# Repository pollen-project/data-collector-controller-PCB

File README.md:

# data-collector-controller-PCB

Design files for the data collector made with KiCAD version 8.0.

## PDF files
* [Schematic](Pollen%20PCB/prints/pollen_sch.pdf)
* [Board](Pollen%20PCB/prints/pollen_pcb.pdf)

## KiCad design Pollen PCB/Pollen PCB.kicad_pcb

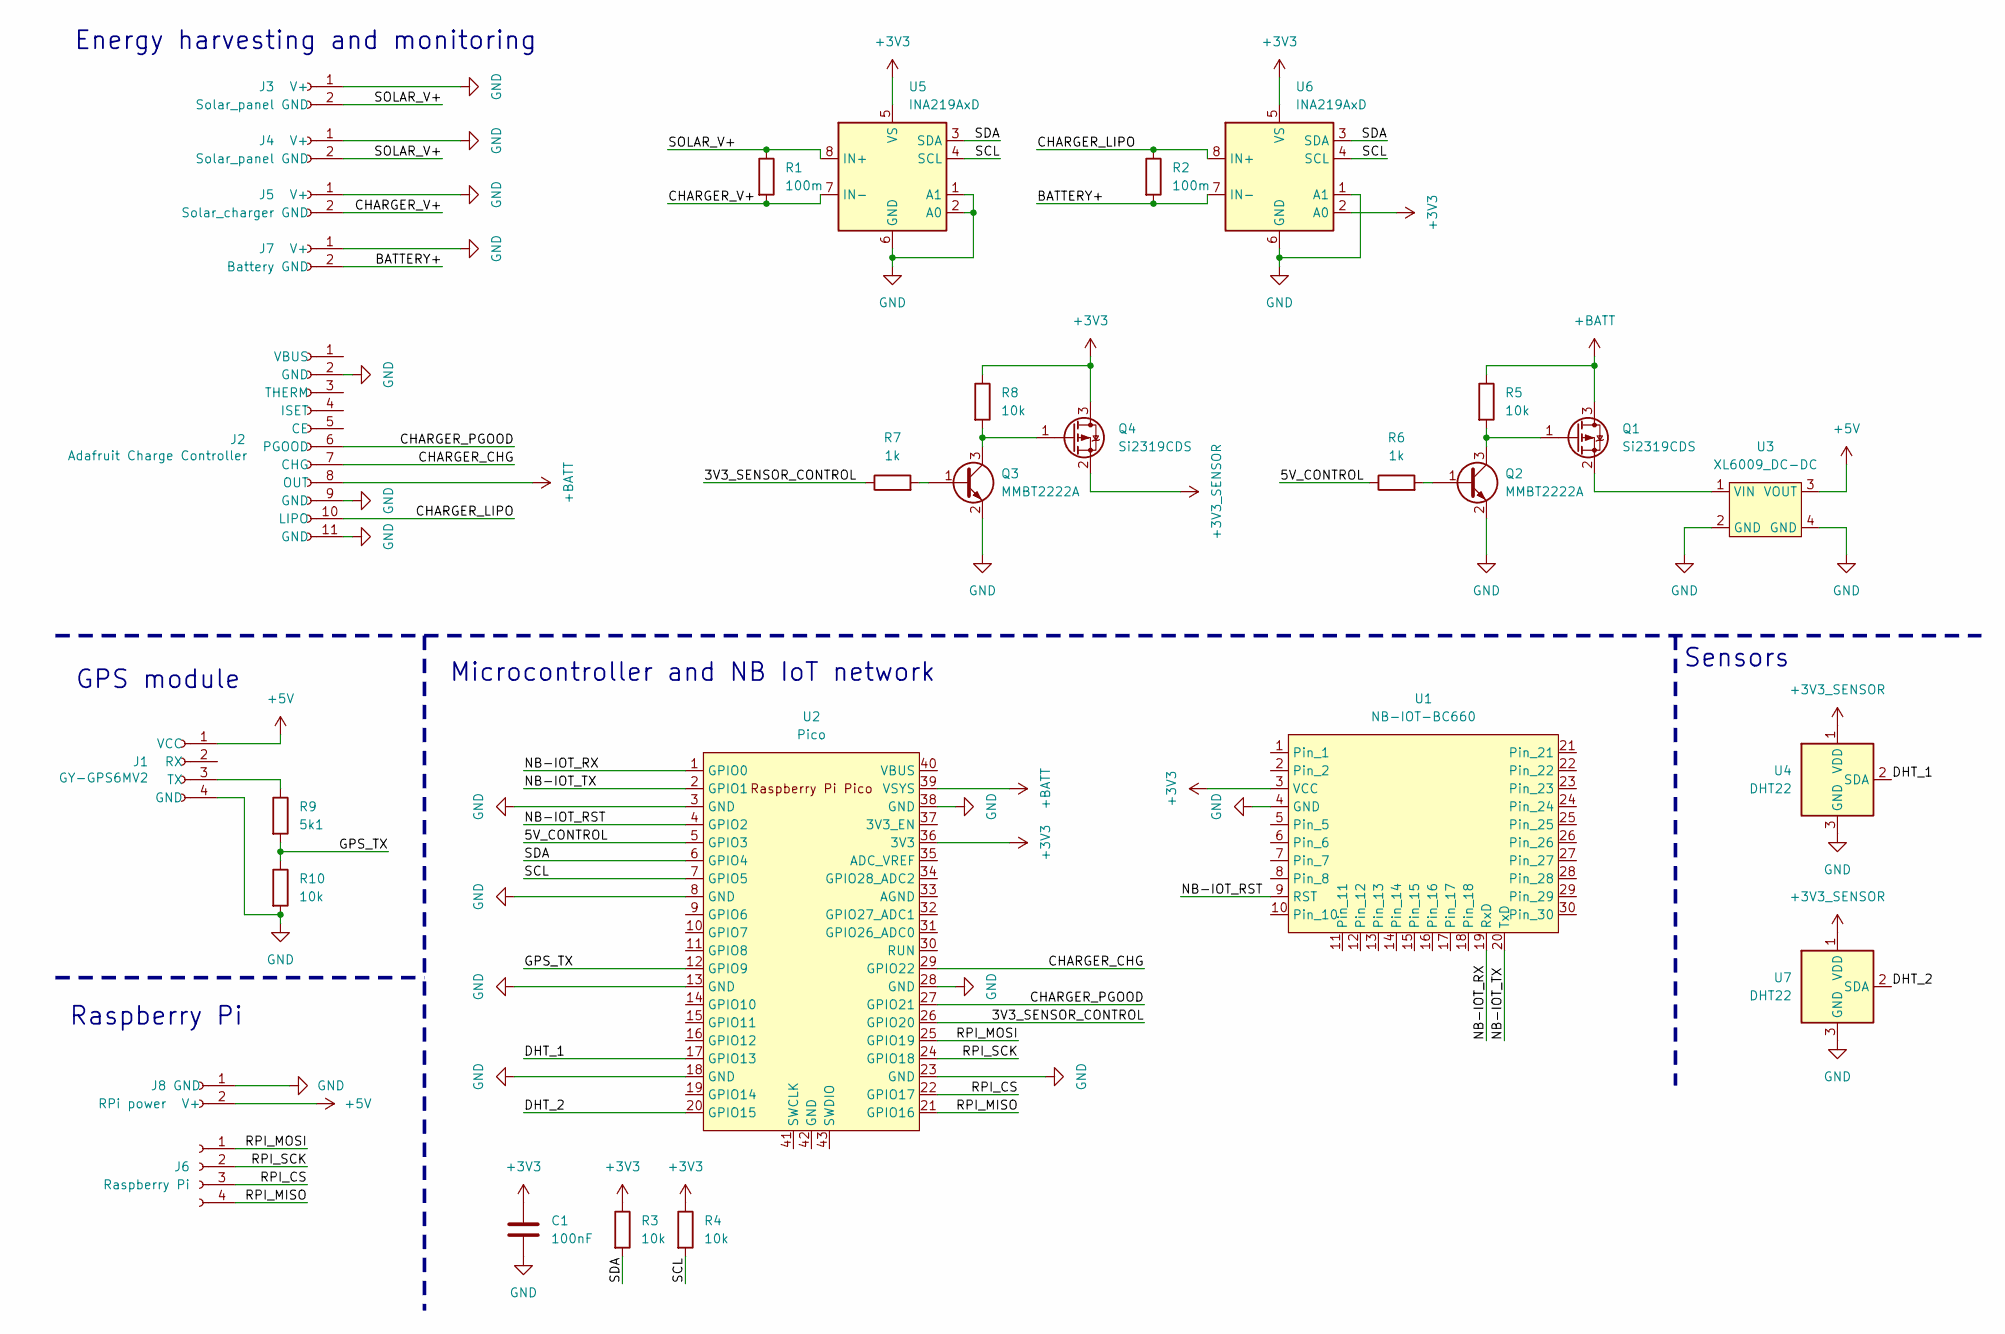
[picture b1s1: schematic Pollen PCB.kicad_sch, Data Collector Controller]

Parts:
C1: 100nF; C_1206_3216Metric_Pad1.33x1.80mm_HandSolder
J1: GY-GPS6MV2; PinSocket_1x04_P2.54mm_Vertical
J2: Adafruit Charge Controller; PinSocket_1x11_P2.54mm_Vertical
J3, J4: Solar_panel; PinSocket_1x02_P2.54mm_Vertical
J5: Solar_charger; PinSocket_1x02_P2.54mm_Vertical
J6: Raspberry Pi; PinSocket_1x04_P2.54mm_Vertical
J7: Battery; PinSocket_1x02_P2.54mm_Vertical
J8: RPi power; PinSocket_1x02_P2.54mm_Vertical
Q1, Q4: Si2319CDS; SOT-23
Q2, Q3: MMBT2222A; SOT-23
R1, R2: 100m; R_2512_6332Metric_Pad1.40x3.35mm_HandSolder
R3, R4, R5, R8, R10: 10k; R_1206_3216Metric_Pad1.30x1.75mm_HandSolder
R6, R7: 1k; R_1206_3216Metric_Pad1.30x1.75mm_HandSolder
R9: 5k1; R_1206_3216Metric_Pad1.30x1.75mm_HandSolder
U1: NB-IOT-BC660
U2: Pico; RPi_Pico_SMD_TH
U3: XL6009_DC-DC
U4, U7: DHT22; ASAIR_AM2302_P2.54mm_Vertical
U5, U6: INA219AxD; SOIC-8_3.9x4.9mm_P1.27mm

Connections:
+3V3: C1.1, Q4.3 (D), R3.1, R4.1, R8.1, U1.3 (VCC), U2.36 (3V3), U5.5 (VS), U6.2 (A0), U6.5 (VS)
+3V3_SENSOR: Q4.2 (S), U4.1 (VDD), U7.1 (VDD)
+5V: J1.1 (VCC), J8.2 (V+), U3.3 (VOUT)
+BATT: J2.8 (OUT), Q1.3 (D), R5.1, U2.39 (VSYS)
/3V3_SENSOR_CONTROL: R7.1, U2.26 (GPIO20)
/5V_CONTROL: R6.1, U2.5 (GPIO3)
/BATTERY+: J7.2 (GND), R2.2, U6.7 (IN-)
/CHARGER_CHG: J2.7 (CHG), U2.29 (GPIO22)
/CHARGER_LIPO: J2.10 (LIPO), R2.1, U6.8 (IN+)
/CHARGER_PGOOD: J2.6 (PGOOD), U2.27 (GPIO21)
/CHARGER_V+: J5.2 (GND), R1.2, U5.7 (IN-)
/DHT_1: U2.17 (GPIO13), U4.2 (SDA)
/DHT_2: U2.20 (GPIO15), U7.2 (SDA)
/GPS_TX: R9.2, R10.1, U2.12 (GPIO9)
/NB-IOT_RST: U1.9 (RST), U2.4 (GPIO2)
/NB-IOT_RX: U1.19 (RxD), U2.1 (GPIO0)
/NB-IOT_TX: U1.20 (TxD), U2.2 (GPIO1)
/RPI_CS: J6.3, U2.22 (GPIO17)
/RPI_MISO: J6.4, U2.21 (GPIO16)
/RPI_MOSI: J6.1, U2.25 (GPIO19)
/RPI_SCK: J6.2, U2.24 (GPIO18)
/SCL: R4.2, U2.7 (GPIO5), U5.4 (SCL), U6.4 (SCL)
/SDA: R3.2, U2.6 (GPIO4), U5.3 (SDA), U6.3 (SDA)
/SOLAR_V+: J3.2 (GND), J4.2 (GND), R1.1, U5.8 (IN+)
GND: C1.2, J1.4 (GND), J2.2 (GND), J2.9 (GND), J2.11 (GND), J3.1 (V+), J4.1 (V+), J5.1 (V+), J7.1 (V+), J8.1 (GND), Q2.2 (E), Q3.2 (E), R10.2, U1.4 (GND), U2.3 (GND), U2.8 (GND), U2.13 (GND), U2.18 (GND), U2.23 (GND), U2.28 (GND), U2.38 (GND), U3.2 (GND), U3.4 (GND), U4.3 (GND), U4.4 (GND), U5.1 (A1), U5.2 (A0), U5.6 (GND), U6.1 (A1), U6.6 (GND), U7.3 (GND), U7.4 (GND)
unnamed: J1.3 (TX), R9.1
unnamed: Q1.1 (G), Q2.3 (C), R5.2
unnamed: Q1.2 (S), U3.1 (VIN)
unnamed: Q2.1 (B), R6.2
unnamed: Q3.1 (B), R7.2
unnamed: Q3.3 (C), Q4.1 (G), R8.2

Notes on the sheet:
Raspberry Pi
Microcontroller and NB IoT network
Sensors
GPS module
Energy harvesting and monitoring

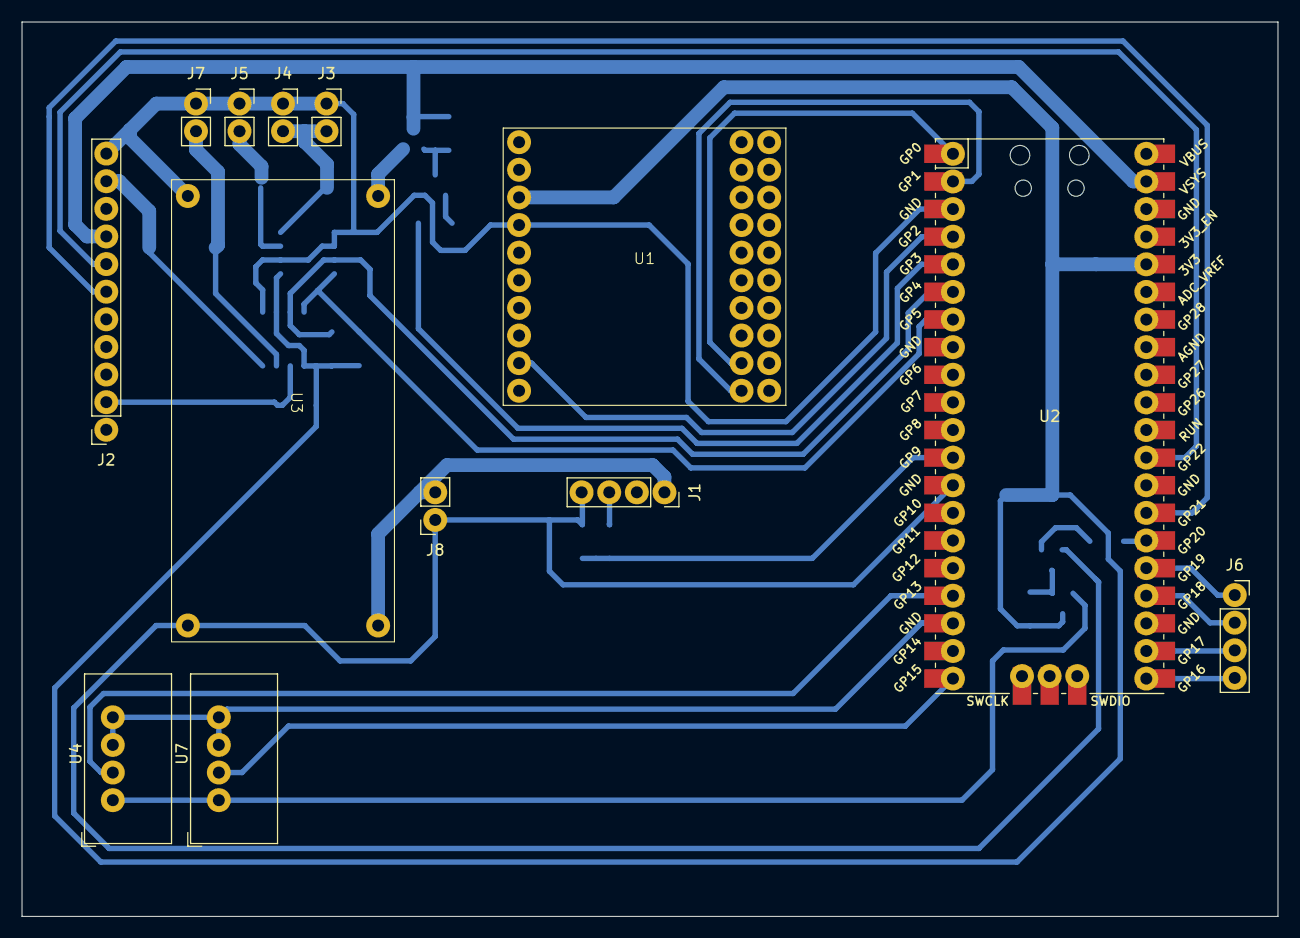
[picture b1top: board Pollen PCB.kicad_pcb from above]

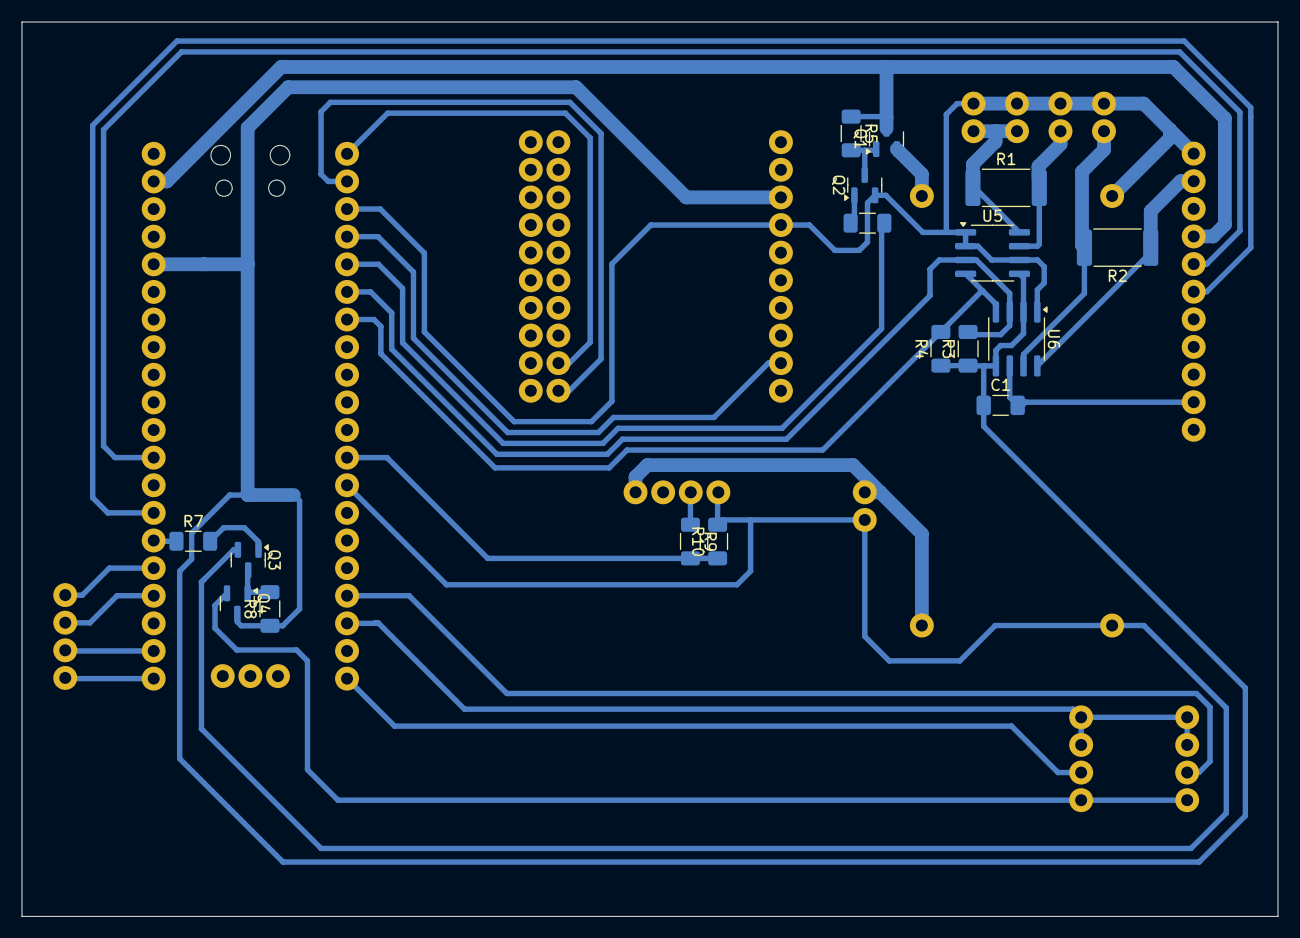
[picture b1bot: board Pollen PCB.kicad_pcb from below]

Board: 2 copper layers, 115.5 x 82.2 mm, 30 parts (17 on the bottom side), 31 nets.

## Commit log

2024-10-24 PCB files start
2024-10-24 Start drawing the schematic
2024-10-25 Schematic v1.0
2024-10-29 PCB footprints organised
2024-10-29 Updated PCB + footprints
2024-10-29 Update PCB
2024-11-01 PCB first try
2024-11-21 Larger vias
2024-12-11 Generate fab files
2024-12-11 Link to prints in the readme
2025-03-31 Add renders
